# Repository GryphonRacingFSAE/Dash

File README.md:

# Gryphon Racing Dash

## About

An electronic dash for Gryphon Racing Vechicles 22-Present

## Installing Dependencies

### Setup for Raspberry Pi

Install all missing packages
```bash
sudo apt-get install python cmake libgl-dev libx11-dev libx11-xcb-dev libxcb-util-dev m4 libffi-dev
```

Ensure that the can interface on the RPi is active
```bash
sudo ip link set can0 up type can bitrate 1000000 # 1 mbps speed
```

### Setup for Windows

- Install [Python](https://docs.python.org/3/using/windows.html#using-python-on-windows) & ensure it is installed to PATH.
- Install [CMake](https://cmake.org/download/) & ensure it is installed to PATH.
- Install [Visual Studio 2022](https://visualstudio.microsoft.com/) & ensure the Desktop Development C++ extension is installed.

### Setup for MacOS
- Ensure python3 version is up to date >3.7
- Install [CMake](https://cmake.org/download/) & ensure it is installed to PATH.

### Universal
- Install conan via pip
```bash
python -m pip install conan==1.60.0 # or python3 on MacOS
```

## Installing Build Dependencies

Run the conan install script (`-pr` is the profile being used, the options are found in [ConanProfiles](./ConanProfiles/))
```bash
# Windows VS2022
conan install . -if build -pr:h=ConanProfiles/VS2022-Debug.ini -pr:b=ConanProfiles/VS2022-Debug.ini --build=missing -o dev="front"

# MacOS clang 14
conan install . -if build -pr:h=ConanProfiles/MacOS-clang-Debug.ini -pr:b=ConanProfiles/MacOS-clang-Debug.ini --build=missing -o dev="front"

# RPi 4b (gcc 10.2)
conan install . -if build -pr:h=ConanProfiles/pi4b-Debug.ini -pr:b=ConanProfiles/pi4b-Debug.ini --build=missing -o dev="full"

# RPi 1.2 b+ (gcc 10.2)
conan install . -if build -pr:h ConanProfiles/pib+-Release.ini -pr:b ConanProfiles/pib+-Release.ini --build=missing

# Linux gcc 12
conan install . -if build -pr:h=ConanProfiles/Linux-gcc-12-Debug.ini -pr:b=ConanProfiles/Linux-gcc-12-Debug.ini --build=missing -o dev="full"
```

* If building with `dev="back"`, Qt is not a requirement

## Building
- Run the conan build script & executables will be found in the build/bin folder.

```bash
conan build -if build .
```

## Running

```bash
source build/activate_run.sh # RPi (maybe required on other linux distros)
./build/Debug/bin/GryphonDash #(This runs the executable on RPi)
./build/bin/GryphonDash.exe #(This is to run the executable on windows)
source build/deactivate_run.sh # RPi (maybe required on other linux distros)
```

## Branch rules

- Name your branch as follows: `firstname/branchtopic`, ex. `dallas/move-from-previous-repo`
- `main` is a protected branch, and thus needs a PR to approve merging with it.

## CAN reservations

| Item | Reserved CAN Addresses |
|-|-|
| Motor Controller | 0x0A0-0x0CF |
| VCU | 0x0D0-0x0DF |
| BMS | 0x0E0-0x0EF |

## Building For RPI1.2

```bash
docker build
docker run
docker cp # copy artifacts back to userspace
```

## Resources

* [<linux/can.h>](https://github.com/torvalds/linux/blob/master/include/uapi/linux/can.h)
* [SocketCAN Intro](https://copperhilltech.com/what-is-socketcan/)
* [PiCAN1](https://copperhilltech.com/pican-with-gps-gyro-accelerometer-can-bus-board-for-raspberry-pi/)/[PiCAN2](https://copperhilltech.com/pican-2-can-bus-interface-for-raspberry-pi/)
* [Raspberry Pi w/ CanBus](https://www.hackster.io/youness/how-to-connect-raspberry-pi-to-can-bus-b60235)
* Not used, but good cross reference for the SocketCAN intro: [socketcan-cpp](https://github.com/siposcsaba89/socketcan-cpp)

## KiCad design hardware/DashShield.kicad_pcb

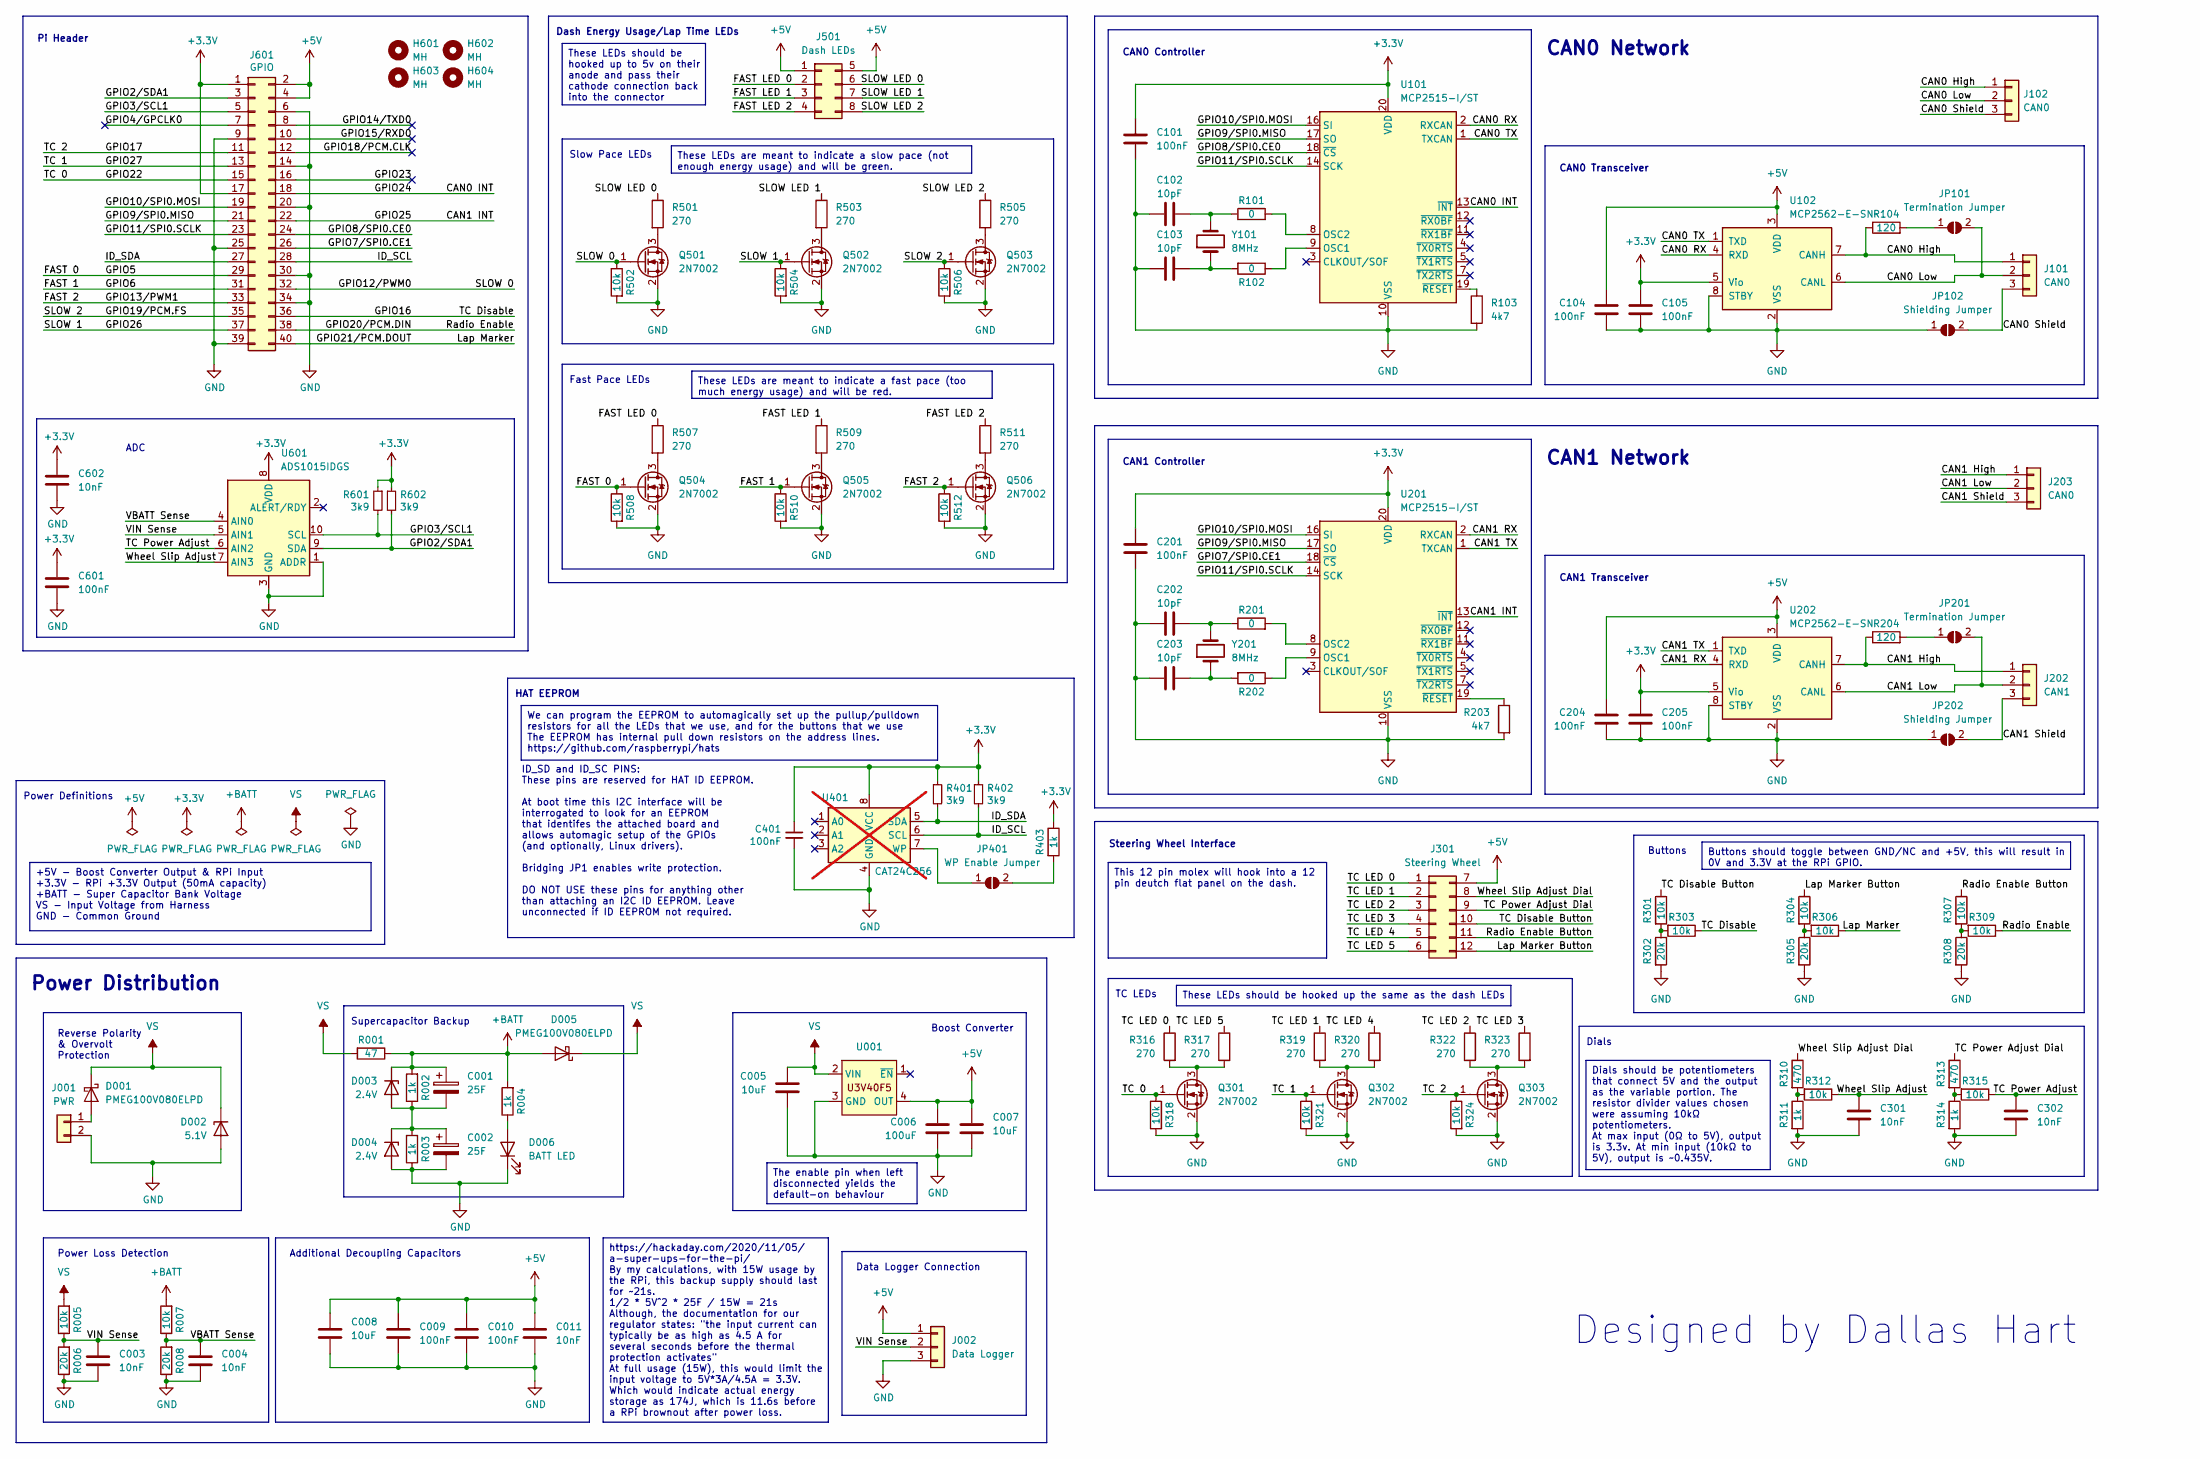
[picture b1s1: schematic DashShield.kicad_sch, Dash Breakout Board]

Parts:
C001, C002: 25F; CP_Radial_D16.0mm_P7.50mm
C003, C004, C011, C301, C302, C602: 10nF; C_0603_1608Metric; LCSC C57112
C005, C007, C008: 10uF; C_0603_1608Metric; LCSC C19702
C006: 100uF; C_1206_3216Metric; LCSC C15008
C009, C010, C101, C104, C105, C201, C204, C205, C401, C601: 100nF; C_0603_1608Metric; LCSC C14663
C102, C103, C202, C203: 10pF; C_0603_1608Metric; LCSC C1634
D001, D005: PMEG100V080ELPD; Nexperia_CFP15_SOT-1289; LCSC C458185
D002: 5.1V; D_SMB; LCSC C2940070
D003, D004: 2.4V; SOT-23; LCSC C411194
D006: BATT LED; LED_0603_1608Metric; LCSC C72038
H601, H602, H603, H604: MH; MountingHole_2.7mm_M2.5_Pad
J001: PWR; Molex_Micro-Fit_3.0_43650-0215_1x02_P3.00mm_Vertical
J002: Data Logger; Molex_Micro-Fit_3.0_43650-0315_1x03_P3.00mm_Vertical
J101, J102, J203: CAN0; Molex_Micro-Fit_3.0_43650-0315_1x03_P3.00mm_Vertical
J202: CAN1; Molex_Micro-Fit_3.0_43650-0315_1x03_P3.00mm_Vertical
J301: Steering Wheel; Molex_Micro-Fit_3.0_43045-1212_2x06_P3.00mm_Vertical
J501: Dash LEDs; Molex_Micro-Fit_3.0_43045-0812_2x04_P3.00mm_Vertical
J601: GPIO; PinSocket_2x20_P2.54mm_Vertical
JP101, JP201: Termination Jumper; SolderJumper-2_P1.3mm_Open_RoundedPad1.0x1.5mm
JP102, JP202: Shielding Jumper; SolderJumper-2_P1.3mm_Open_RoundedPad1.0x1.5mm
JP401: WP Enable Jumper; SolderJumper-2_P1.3mm_Open_RoundedPad1.0x1.5mm
Q301, Q302, Q303, Q501, Q502, Q503, Q504, Q505, Q506: 2N7002; SOT-23; LCSC C8545
R001: 47; R_2512_6332Metric; LCSC C2913007
R002, R003, R004, R311, R314, R403: 1k; R_0603_1608Metric; LCSC C21190
R005, R007, R301, R303, R304, R306, R307, R309, R312, R315, R318, R321, R324, R502, R504, R506, R508, R510, R512: 10k; R_0603_1608Metric; LCSC C25804
R006, R008, R302, R305, R308: 20k; R_0603_1608Metric; LCSC C4184
R101, R102, R201, R202: 0; R_0603_1608Metric; LCSC C21189
R103, R203: 4k7; R_0603_1608Metric; LCSC C23162
R104, R204: 120; R_0603_1608Metric; LCSC C22787
R310, R313: 470; R_0603_1608Metric; LCSC C23179
R316, R317, R319, R320, R322, R323, R501, R503, R505, R507, R509, R511: 270; R_0603_1608Metric; LCSC C22966
R401, R402, R601, R602: 3k9; R_0603_1608Metric; LCSC C23018
U001: U3V40x
U101, U201: MCP2515-I/ST; TSSOP-20_4.4x6.5mm_P0.65mm; LCSC C15193
U102, U202: MCP2562-E-SN; SOIC-8_3.9x4.9mm_P1.27mm; LCSC C191417
U401: CAT24C256; SOIC-8_3.9x4.9mm_P1.27mm; LCSC C79987; not fitted
U601: ADS1015IDGS; TSSOP-10_3x3mm_P0.5mm; LCSC C193969
Y101, Y201: 8MHz; Crystal_SMD_Abracon_ABM3B-4Pin_5.0x3.2mm; LCSC C276420

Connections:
+3.3V: C101.1, C105.1, C201.1, C205.1, C401.1, C601.1, C602.1, J601.1, J601.17, R401.1, R402.1, R403.1, R601.1, R602.1, U101.20 (VDD), U102.5 (Vio), U201.20 (VDD), U202.5 (Vio), U401.8 (VCC), U601.8 (VDD)
+5V: C006.1, C007.1, C008.1, C009.1, C010.1, C011.1, C104.1, C204.1, J002.1, J301.7, J501.1, J501.5, J601.2, J601.4, U001.4 (OUT), U102.3 (VDD), U202.3 (VDD)
+BATT: C001.1, D003.3 (K), D005.1 (A), D005.2 (A), R001.1, R002.2, R004.2, R007.2
/CAN0 High: J101.1, J102.1, R104.1, U102.7 (CANH)
/CAN0 INT: J601.18, U101.13 (~INT)
/CAN0 Low: J101.2, J102.2, JP101.2 (B), U102.6 (CANL)
/CAN0 RX: U101.2 (RXCAN), U102.4 (RXD)
/CAN0 Shield: J101.3, J102.3, JP102.2 (B)
/CAN0 TX: U101.1 (TXCAN), U102.1 (TXD)
/CAN1 High: J202.1, J203.1, R204.1, U202.7 (CANH)
/CAN1 INT: J601.22, U201.13 (~INT)
/CAN1 Low: J202.2, J203.2, JP201.2 (B), U202.6 (CANL)
/CAN1 RX: U201.2 (RXCAN), U202.4 (RXD)
/CAN1 Shield: J202.3, J203.3, JP202.2 (B)
/CAN1 TX: U201.1 (TXCAN), U202.1 (TXD)
/FAST 0: J601.29, Q504.1 (G), R508.1
/FAST 1: J601.31, Q505.1 (G), R510.1
/FAST 2: J601.33, Q506.1 (G), R512.1
/FAST LED 0: J501.2, R507.1
/FAST LED 1: J501.3, R509.1
/FAST LED 2: J501.4, R511.1
/GPIO2/SDA1: J601.3, R602.2, U601.9 (SDA)
/GPIO3/SCL1: J601.5, R601.2, U601.10 (SCL)
/GPIO4/GPCLK0: J601.7
/GPIO7/SPI0.CE1: J601.26, U201.18 (~CS)
/GPIO8/SPI0.CE0: J601.24, U101.18 (~CS)
/GPIO9/SPI0.MISO: J601.21, U101.17 (SO), U201.17 (SO)
/GPIO10/SPI0.MOSI: J601.19, U101.16 (SI), U201.16 (SI)
/GPIO11/SPI0.SCLK: J601.23, U101.14 (SCK), U201.14 (SCK)
/GPIO12/PWM0: J601.32, Q501.1 (G), R502.1
/GPIO14/TXD0: J601.8
/GPIO15/RXD0: J601.10
/GPIO16: J601.36, R303.1
/GPIO17: J601.11, Q303.1 (G), R324.1
/GPIO18/PCM.CLK: J601.12
/GPIO19/PCM.FS: J601.35, Q503.1 (G), R506.1
/GPIO20/PCM.DIN: J601.38, R309.1
/GPIO21/PCM.DOUT: J601.40, R306.1
/GPIO22: J601.15, Q301.1 (G), R318.1
/GPIO23: J601.16
/GPIO26: J601.37, Q502.1 (G), R504.1
/GPIO27: J601.13, Q302.1 (G), R321.1
/ID_SCL: J601.28, R402.2, U401.6 (SCL)
/ID_SDA: J601.27, R401.2, U401.5 (SDA)
/Lap Marker Button: J301.12, R304.1
/Radio Enable Button: J301.11, R307.1
/SLOW LED 0: J501.6, R501.1
/SLOW LED 1: J501.7, R503.1
/SLOW LED 2: J501.8, R505.1
/TC Disable Button: J301.10, R301.1
/TC LED 0: J301.1, R316.1
/TC LED 1: J301.2, R319.1
/TC LED 2: J301.3, R322.1
/TC LED 3: J301.4, R323.1
/TC LED 4: J301.5, R320.1
/TC LED 5: J301.6, R317.1
/TC Power Adjust: C302.1, R315.1, U601.6 (AIN2)
/TC Power Adjust Dial: J301.9, R313.1
/VBATT Sense: C004.1, R007.1, R008.2, U601.4 (AIN0)
/VIN Sense: C003.1, J002.2, R005.1, R006.2, U601.5 (AIN1)
/Wheel Slip Adjust: C301.1, R312.1, U601.7 (AIN3)
/Wheel Slip Adjust Dial: J301.8, R310.1
GND: C002.2, C003.2, C004.2, C005.2, C006.2, C007.2, C008.2, C009.2, C010.2, C011.2, C101.2, C102.2, C103.1, C104.2, C105.2, C201.2, C202.2, C203.1, C204.2, C205.2, C301.2, C302.2, C401.2, C601.2, C602.2, D002.2 (A), D004.1 (A), D006.1 (K), J001.2, J002.3, J601.6, J601.9, J601.14, J601.20, J601.25, J601.30, J601.34, J601.39, JP102.1 (A), JP202.1 (A), Q301.2 (S), Q302.2 (S), Q303.2 (S), Q501.2 (S), Q502.2 (S), Q503.2 (S), Q504.2 (S), Q505.2 (S), Q506.2 (S), R003.1, R006.1, R008.1, R103.2, R203.2, R302.2, R305.2, R308.2, R311.2, R314.2, R318.2, R321.2, R324.2, R502.2, R504.2, R506.2, R508.2, R510.2, R512.2, U001.3 (GND), U101.10 (VSS), U102.2 (VSS), U102.8 (STBY), U201.10 (VSS), U202.2 (VSS), U202.8 (STBY), U401.4 (GND), U601.1 (ADDR), U601.3 (GND)
unnamed: C102.1, R101.1, Y101.2
unnamed: C103.2, R102.2, Y101.1
unnamed: C202.1, R201.1, Y201.2
unnamed: C203.2, R202.2, Y201.1
unnamed: C001.2, C002.1, D003.1 (A), D004.3 (K), R002.1, R003.2
unnamed: D006.2 (A), R004.1
unnamed: D001.1 (A), D001.2 (A), J001.1
unnamed: JP101.1 (A), R104.2
unnamed: JP201.1 (A), R204.2
unnamed: JP401.1 (A), U401.7 (WP)
unnamed: JP401.2 (B), R403.2
unnamed: Q301.3 (D), R316.2, R317.2
unnamed: Q302.3 (D), R319.2, R320.2
unnamed: Q303.3 (D), R322.2, R323.2
unnamed: Q501.3 (D), R501.2
unnamed: Q502.3 (D), R503.2
unnamed: Q503.3 (D), R505.2
unnamed: Q504.3 (D), R507.2
unnamed: Q505.3 (D), R509.2
unnamed: Q506.3 (D), R511.2
unnamed: R301.2, R302.1, R303.2
unnamed: R304.2, R305.1, R306.2
unnamed: R307.2, R308.1, R309.2
unnamed: R310.2, R311.1, R312.2
unnamed: R313.2, R314.1, R315.2
unnamed: R102.1, U101.9 (OSC1)
unnamed: R101.2, U101.8 (OSC2)
unnamed: R103.1, U101.19 (~RESET)
unnamed: R202.1, U201.9 (OSC1)
unnamed: R201.2, U201.8 (OSC2)
unnamed: R203.1, U201.19 (~RESET)
VS: C005.1, D001.3 (K), D002.1 (K), D005.3 (K), R001.2, R005.2, U001.2 (VIN)

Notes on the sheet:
https://hackaday.com/2020/11/05/ a-super-ups-for-the-pi/ By my calculations, with 15W usage by the RPi, this backup supply should last for ~21s. 1/2 * 5V^2 * 25F / 15W = 21s Although, the documentation for our regulator states: "the input current can typically be as high as 4.5 A for several second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
These LEDs should be hooked up to 5v on their anode and pass their cathode connection back into the connector
Buttons should toggle between GND/NC and +5V, this will result in 0V and 3.3V at the RPi GPIO.
We can program the EEPROM to automagically set up the pullup/pulldown resistors for all the LEDs that we use, and for the buttons that we use The EEPROM has internal pull down resistors on the address lines. https://github.com/raspberrypi/hats
The enable pin when left disconnected yields the default-on behaviour
These LEDs are meant to indicate a slow pace (not enough energy usage) and will be green.
Dials should be potentiometers that connect 5V and the output as the variable portion. The resistor divider values chosen were assuming 10kΩ potentiometers. At max input (0Ω to 5V), output is 3.3v. At min input (10kΩ to 5V), output is ~0.435V.
This 12 pin molex will hook into a 12 pin deutch flat panel on the dash.
+5V - Boost Converter Output & RPi Input +3.3V - RPi +3.3V Output (50mA capacity) +BATT - Super Capacitor Bank Voltage VS - Input Voltage from Harness GND - Common Ground
These LEDs should be hooked up the same as the dash LEDs
These LEDs are meant to indicate a fast pace (too much energy usage) and will be red.
Power Loss Detection
Power Definitions
CAN1 Controller
Reverse Polarity & Overvolt Protection
Dials
Designed by Dallas Hart
ID_SD and ID_SC PINS: These pins are reserved for HAT ID EEPROM. At boot time this I2C interface will be interrogated to look for an EEPROM that identifes the attached board and allows automagic setup of the GPIOs (and optionally, Linux drivers). Bridging JP1 enables write protection. DO NOT USE th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
ADC
Data Logger Connection
Buttons
Power Distribution
Fast Pace LEDs
TC LEDs
CAN1 Transceiver
Supercapacitor Backup
Steering Wheel Interface
CAN1 Network
Dash Energy Usage/Lap Time LEDs
HAT EEPROM
Slow Pace LEDs
CAN0 Network
Pi Header
CAN0 Transceiver
CAN0 Controller
Additional Decoupling Capacitors
Boost Converter

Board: 4 copper layers, 125 parts (1 on the bottom side), 90 nets, no tracks yet.

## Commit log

2023-10-16 chore: upload progress
2023-10-21 Chore-Upload progress
2023-10-30 feat: add ADC and data logger connector
2023-11-19 rev2
2024-01-19 feat: added pours & pass-through for CAN0&CAN1
2024-01-24 chore: add all LCSC parts and update footprints
2024-01-24 chore: I2C pullups and new WIP layout
2024-03-15 feat/demo
    demo screen
2024-03-15 fix/VCU
2024-03-15 fix/revert
2024-03-15 feat/speedDemo
